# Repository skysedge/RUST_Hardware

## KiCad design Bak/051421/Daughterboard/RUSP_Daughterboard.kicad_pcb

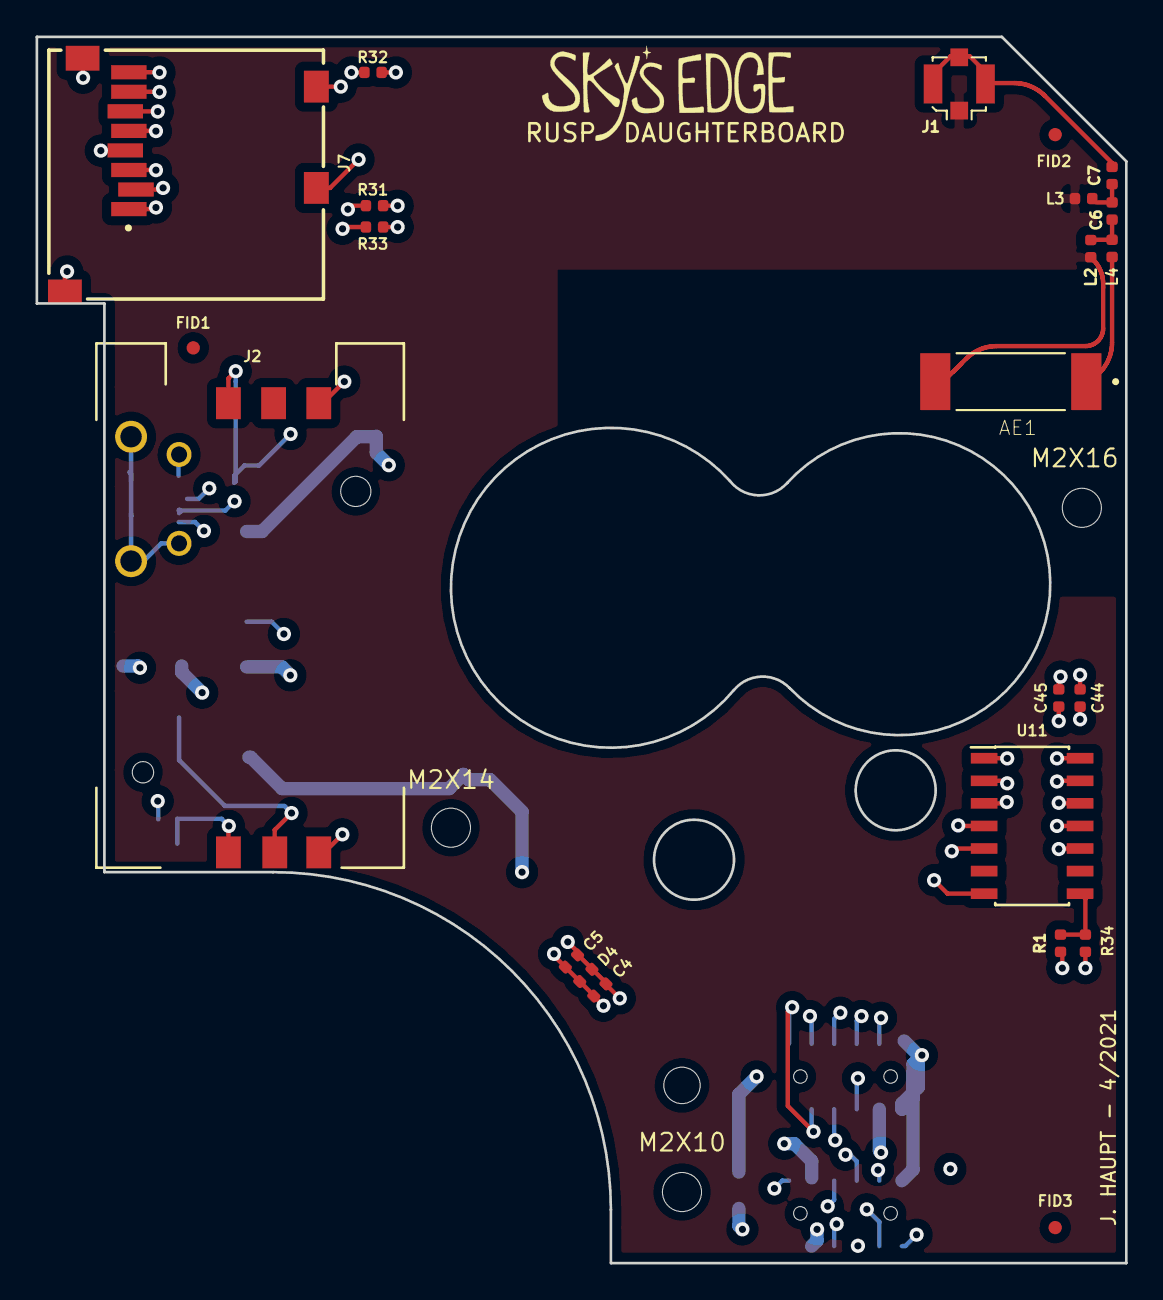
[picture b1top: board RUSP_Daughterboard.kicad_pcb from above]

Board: 4 copper layers, 61.3 x 69.0 mm, 46 parts (0 on the bottom side), 33 nets.

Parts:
AE1: Antenna_Chip; XCVR_NN02-232
C1, C2, C3, C4: 47pF/50V; R_0402_1005Metric
C5: 100nF/16V; R_0402_1005Metric
C6: 2.7pF; C_0402_1005Metric
C7: .5pF; C_0402_1005Metric
C44, C45: .1uF; C_0402_1005Metric
D1, D2, D3, D4: D_TVS; R_0402_1005Metric
D5: D_Schottky; D_SOD-123
D6, D7: 1N4148; D_SOD-123
FID1, FID2, FID3, FID4, FID5, FID6: Fiducial; Fiducial_0.75mm_Dia_1.5mm_Outer
J1: Conn_Coaxial; U.FL_Molex_MCRF_73412-0110_Vertical
J2: SIM; SIMHolder_Amph7111S2015X02LF
J3, J6: Conn_01x12; Samtec_2x6HeaderSocket_FLE-106-01-G-DV
J4: USB_B_Micro; AMPHENOL_MicroUSB_10118194-0001LF
J7: Micro_SD_Card_Det; MicroSDSocket_GCT_MEM2061-01-188-00-A
K1: EE2-3TNU; Relay_Kemet_EE2-3TNU
L1: Ferrite_Bead; R_0805_2012Metric_Pad1.15x1.40mm_HandSolder
L2, L3, L4: 7.5nH; L_0402_1005Metric
LOGO1: Logo1; SkysEdge_18mm
LOGO2: Logo2; SkysEdge_18mm
MH1, MH2, MH4: MountingHole; MountingHole_2.2mm_M2
MH3: MountingHole; MountingHole_2mm
R1: 2k; R_0402_1005Metric
R31, R32, R33: 100k; R_0402_1005Metric
R34: 10k; R_0402_1005Metric
U11: TXB0104D; SOIC-14_3.9x8.7mm_P1.27mm

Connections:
+3V3: C45.1, J6.2, J7.6, R31.1, R32.1, R33.1, U11.1
+3V8: C44.1, J3.2, J3.3, J7.9, K1.4, U11.14
+BATT: J3.11, J3.12, J6.12, K1.3
/CELL_USB_D+: J4.2, J6.10
/CELL_USB_D-: J4.3, J6.11
/LL_OE: J6.5, R1.1
/MISO: J3.5, U11.10
/MOSI: J3.4, U11.12
/POWSW4: D6.1, J3.9, K1.6
/RELAYOFF: D7.1, J6.4, K1.1
/SCK: J3.6, U11.11
/SD CARD/CS_3V3: J7.2, R31.2, U11.2
/SD CARD/DI_3V3: J7.3, U11.3
/SD CARD/DO_3V3: J7.7, U11.5
/SD CARD/SCK_3V3: J7.5, U11.4
/SD_CD: J3.7, J7.10
/SD_CS: J3.8, U11.13
/SIM_CLK: C2.1, D2.1, J2.3, J6.8
/SIM_IO: C1.1, D1.1, J2.7, J6.9
/SIM_RST: C3.1, D3.1, J2.2, J6.7
/VSIM: C4.1, C5.1, D4.1, J2.1, J6.6
GND: C1.2, C2.2, C3.2, C4.2, C5.2, C44.2, C45.2, D1.2, D2.2, D3.2, D4.2, D6.2, D7.2, J2.5, J3.1, J3.10, J4.5, J4.6, J6.1, J7.4, J7.11, K1.7, K1.12, R34.2, U11.7
GNDA: AE1.2, J1.1, L2.2, L3.2
unnamed: AE1.1, L4.1
unnamed: C6.1, L2.1, L4.2
unnamed: C6.2, C7.1, L3.1
unnamed: C7.2, J1.2
unnamed: D5.1, L1.2
unnamed: D5.2, J4.1
unnamed: J7.1, R33.2
unnamed: J7.8, R32.2
unnamed: R1.2, R34.1, U11.8
VBUS: J6.3, L1.1
